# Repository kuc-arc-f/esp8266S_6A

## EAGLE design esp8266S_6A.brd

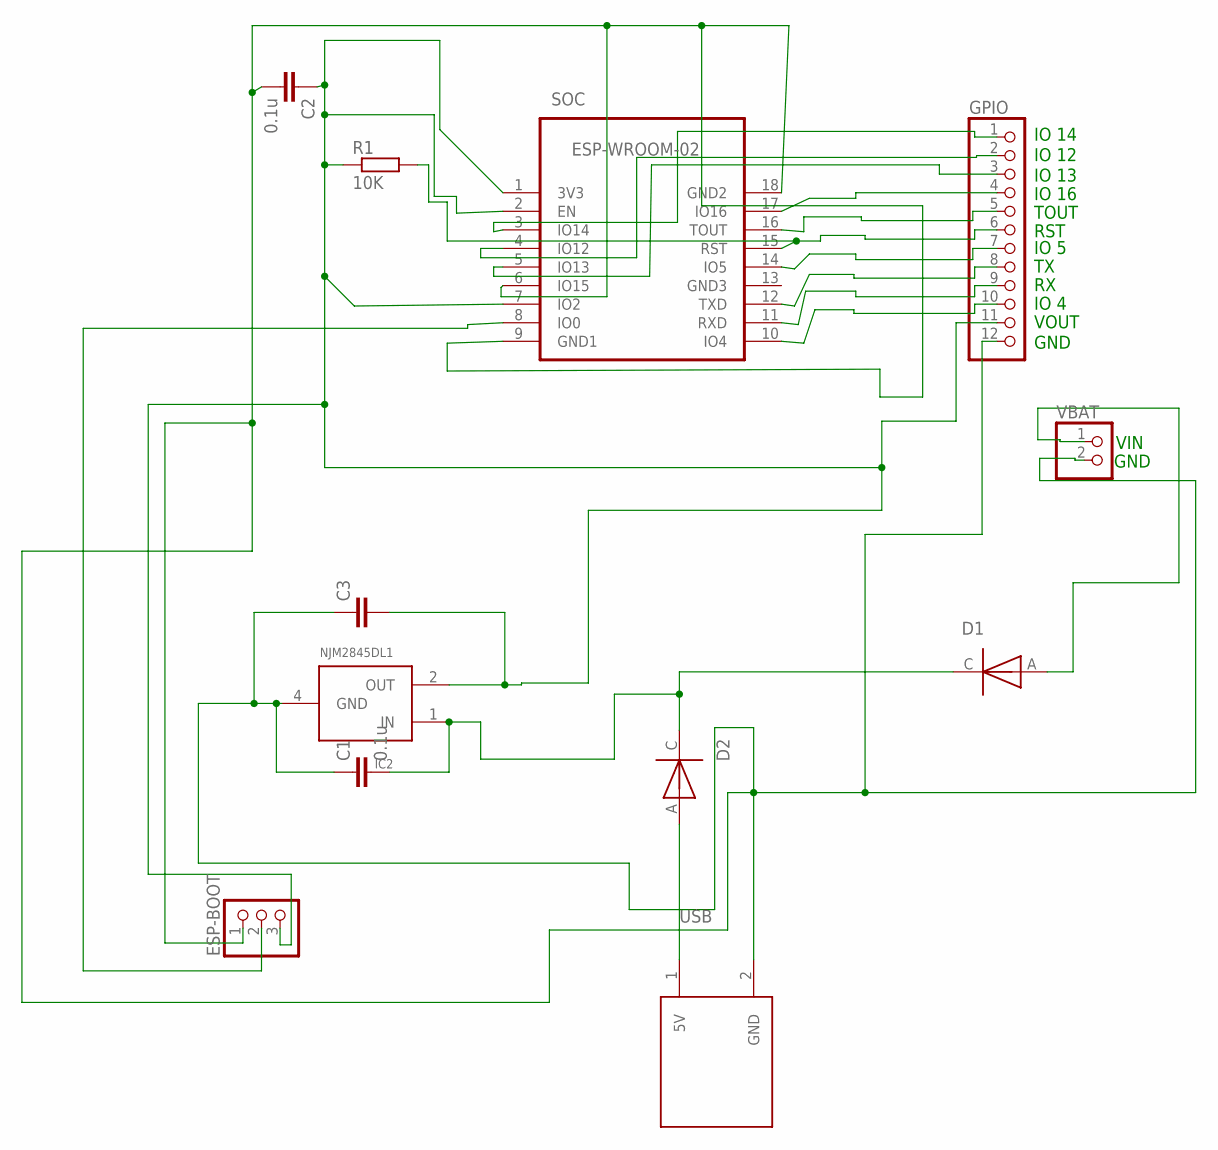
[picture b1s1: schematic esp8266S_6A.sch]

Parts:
C1, C2: 0.1u; C0603
C3: C-EUC1206; C1206
D1, D2: DIODE-EX; SOD80C
ESP-BOOT: PINHD-1X3; 1X03
GPIO: PINHD-1X12; 1X12
IC2: NJM2845DL1; NJM2845DL1-PKG
R1: 10K; R0603
SOC: ESP-WROOM-02; FRONT-FACE-CP2
USB: USB-CUST-1; USB-CUST-1-PKG
VBAT: PINHD-1X2; 1X02

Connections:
unnamed: ESP-BOOT.2, SOC.8 (IO0)
unnamed: GPIO.1, SOC.3 (IO14)
unnamed: C1.2, D1.C, D2.C, IC2.1 (IN)
unnamed: GPIO.4, SOC.17 (IO16)
unnamed: GPIO.5, SOC.16 (TOUT)
unnamed: GPIO.7, SOC.14 (IO5)
unnamed: GPIO.8, SOC.12 (TXD)
unnamed: GPIO.9, SOC.11 (RXD)
unnamed: GPIO.10, SOC.10 (IO4)
unnamed: D2.A, USB.1 (5V)
unnamed: GPIO.6, R1.2, SOC.15 (RST)
unnamed: C2.1, C3.2, ESP-BOOT.3, GPIO.11, IC2.2 (OUT), R1.1, SOC.1 (3V3), SOC.2 (EN), SOC.7 (IO2)
unnamed: D1.A, VBAT.1
unnamed: GPIO.3, SOC.5 (IO13)
unnamed: GPIO.2, SOC.4 (IO12)
unnamed: C1.1, C2.2, C3.1, ESP-BOOT.1, GPIO.12, IC2.4 (GND), SOC.6 (IO15), SOC.9 (GND1), SOC.18 (GND2), USB.2 (GND), VBAT.2

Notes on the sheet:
IO 16
IO 13
IO 12
IO 14
TOUT
RST
IO 5
IO 4
VOUT
GND
VIN

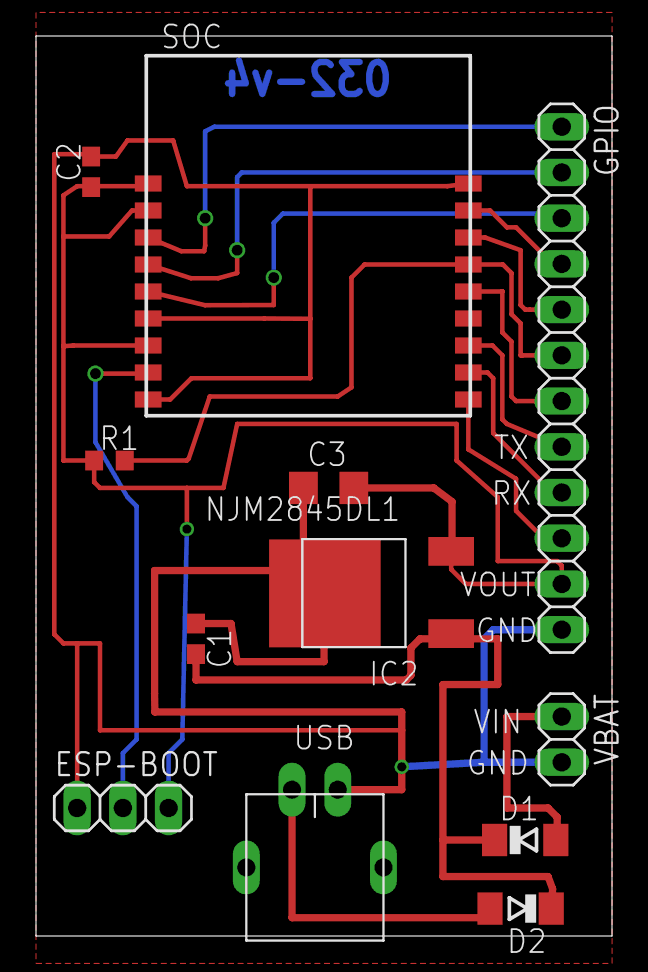
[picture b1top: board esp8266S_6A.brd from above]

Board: 2 copper layers, 32.0 x 50.0 mm, 12 parts (0 on the bottom side), 16 nets.

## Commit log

2017-08-17 new, 08-17a1
